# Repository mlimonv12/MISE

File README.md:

View this project on [CADLAB.io](https://cadlab.io/project/28877). 

# MISE

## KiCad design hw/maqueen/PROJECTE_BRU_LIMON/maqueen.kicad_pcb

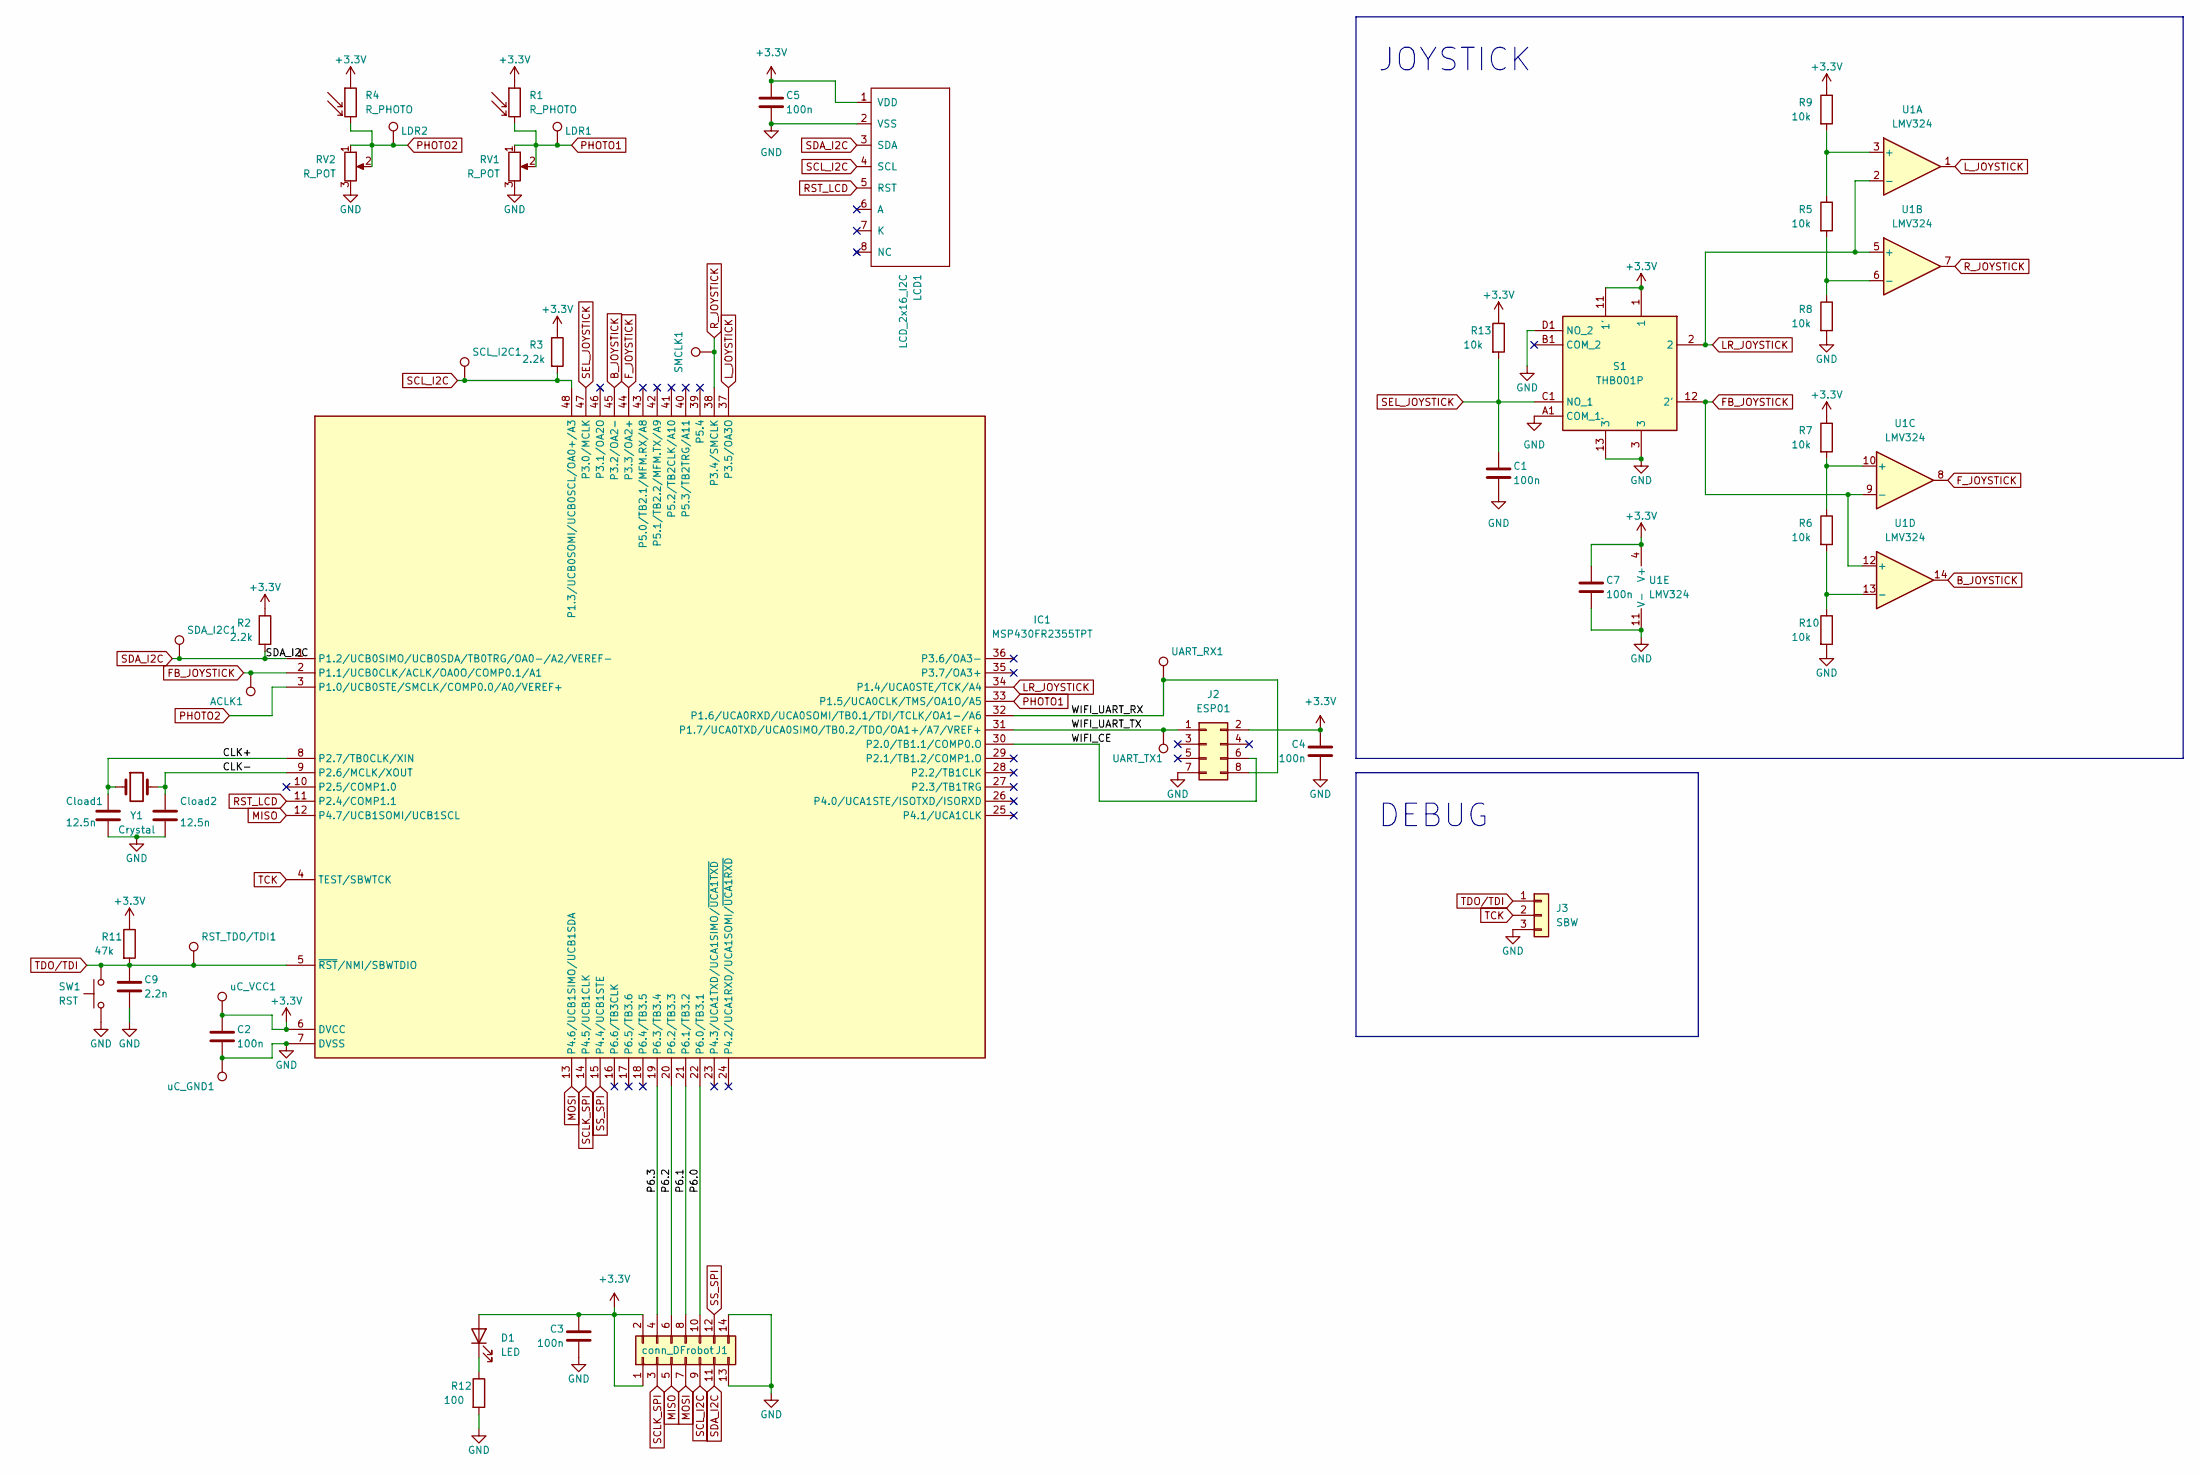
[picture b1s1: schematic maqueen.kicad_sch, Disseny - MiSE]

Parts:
ACLK1: PinHeader_1x01_P2.54mm_Vertical
C1, C2, C3, C4, C5, C7: 100n; C_0805_2012Metric
C9: 2.2n; C_0805_2012Metric
Cload1, Cload2: 12.5n; C_0805_2012Metric
D1: LED; LED_D1.8mm_W3.3mm_H2.4mm
IC1: MSP430FR2355TPT; QFP50P900X900X160-48N; Manufacturer_Part_Number MSP430FR2355TPT; Mouser Part Number 595-MSP430FR2355TPT
J1: conn_DFrobot
J2: ESP01; PinHeader_2x04_P2.54mm_Vertical
J3: SBW; PinHeader_1x03_P2.54mm_Vertical
LCD1: LCD_2x16_I2C; LCD_2x16_I2C(Midas)
LDR1, LDR2: PinHeader_1x01_P2.54mm_Vertical
R1, R4: R_PHOTO; LDR
R2, R3: 2.2k; R_0805_2012Metric
R5, R6, R7, R8, R9, R10, R13: 10k; R_0805_2012Metric
R11: 47k; R_0805_2012Metric
R12: 100; R_0805_2012Metric
RST_TDO/TDI1: PinHeader_1x01_P2.54mm_Vertical
RV1, RV2: R_POT; Trimmer_MiSE
S1: THB001P; Manufacturer_Part_Number THB001P; Mouser Part Number 611-THB001P
SCL_I2C1: PinHeader_1x01_P2.54mm_Vertical
SDA_I2C1: PinHeader_1x01_P2.54mm_Vertical
SMCLK1: PinHeader_1x01_P2.54mm_Vertical
SW1: RST; SW_PUSH_6mm
U1: LMV324; SOIC-14_3.9x8.7mm_P1.27mm
UART_RX1: PinHeader_1x01_P2.54mm_Vertical
UART_TX1: PinHeader_1x01_P2.54mm_Vertical
Y1: Crystal; PinHeader_1x02_P1.27mm_Vertical
uC_GND1: PinHeader_1x01_P2.54mm_Vertical
uC_VCC1: PinHeader_1x01_P2.54mm_Vertical

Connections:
+3.3V: C2.1, C3.1, C4.1, C5.1, C7.1, D1.2 (A), IC1.6 (DVCC), J1.1, J1.2, J2.2, LCD1.1 (VDD), R1.1, R2.1, R3.1, R4.1, R7.1, R9.1, R11.1, R13.1, S1.1, S1.11 (1'), U1.4 (V+), uC_VCC1.1
/CLK+: Cload1.1, IC1.8 (P2.7/TB0CLK/XIN), Y1.1
/CLK-: Cload2.1, IC1.9 (P2.6/MCLK/XOUT), Y1.2
/P6.0: IC1.22 (P6.0/TB3.1), J1.10
/P6.1: IC1.21 (P6.1/TB3.2), J1.8
/P6.2: IC1.20 (P6.2/TB3.3), J1.6
/P6.3: IC1.19 (P6.3/TB3.4), J1.4
/WIFI_CE: IC1.30 (P2.0/TB1.1/COMP0.O), J2.6
/WIFI_UART_RX: IC1.32 (P1.6/UCA0RXD/UCA0SOMI/TB0.1/TDI/TCLK/OA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), J2.8, UART_RX1.1
/WIFI_UART_TX: IC1.31 (P1.7/UCA0TXD/UCA0SIMO/TB0.2/TDO/OA1+/A7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), J2.1, UART_TX1.1
B_JOYSTICK: IC1.45 (P3.2/OA2-), U1.14
FB_JOYSTICK: ACLK1.1, IC1.2 (P1.1/UCB0CLK/ACLK/OA0O/COMP0.1/A1), S1.12 (2'), U1.9 (-), U1.12 (+)
F_JOYSTICK: IC1.44 (P3.3/OA2+), U1.8
GND: C1.2, C2.2, C3.2, C4.2, C5.2, C7.2, C9.2, Cload1.2, Cload2.2, IC1.7 (DVSS), J1.13, J1.14, J2.7, J3.3, LCD1.2 (VSS), R8.2, R10.2, R12.2, RV1.3, RV2.3, S1.3, S1.13 (3'), S1.A1 (COM_1), S1.D1 (NO_2), SW1.1, U1.11 (V-), uC_GND1.1
LR_JOYSTICK: IC1.34 (P1.4/UCA0STE/TCK/A4), S1.2, U1.2 (-), U1.5 (+)
L_JOYSTICK: IC1.37 (P3.5/OA3O), U1.1
MISO: IC1.12 (P4.7/UCB1SOMI/UCB1SCL), J1.5
MOSI: IC1.13 (P4.6/UCB1SIMO/UCB1SDA), J1.7
unnamed: D1.1 (K), R12.1
unnamed: R5.1, R9.2, U1.3 (+)
unnamed: R5.2, R8.1, U1.6 (-)
unnamed: R6.1, R7.2, U1.10 (+)
unnamed: R6.2, R10.1, U1.13 (-)
PHOTO1: IC1.33 (P1.5/UCA0CLK/TMS/OA1O/A5), LDR1.1, R1.2, RV1.1, RV1.2
PHOTO2: IC1.3 (P1.0/UCB0STE/SMCLK/COMP0.0/A0/VEREF+), LDR2.1, R4.2, RV2.1, RV2.2
RST_LCD: IC1.11 (P2.4/COMP1.1), LCD1.5 (RST)
R_JOYSTICK: IC1.38 (P3.4/SMCLK), SMCLK1.1, U1.7
SCLK_SPI: IC1.14 (P4.5/UCB1CLK), J1.3
SCL_I2C: IC1.48 (P1.3/UCB0SOMI/UCB0SCL/OA0+/A3), J1.9, LCD1.4 (SCL), R3.2, SCL_I2C1.1
SDA_I2C: IC1.1 (P1.2/UCB0SIMO/UCB0SDA/TB0TRG/OA0-/A2/VE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), J1.11, LCD1.3 (SDA), R2.2, SDA_I2C1.1
SEL_JOYSTICK: C1.1, IC1.47 (P3.0/MCLK), R13.2, S1.C1 (NO_1)
SS_SPI: IC1.15 (P4.4/UCB1STE), J1.12
TCK: IC1.4 (TEST/SBWTCK), J3.2
TDO/TDI: C9.1, IC1.5 (~RST/NMI/SBWTDIO), J3.1, R11.2, RST_TDO/TDI1.1, SW1.2

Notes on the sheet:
DEBUG
JOYSTICK

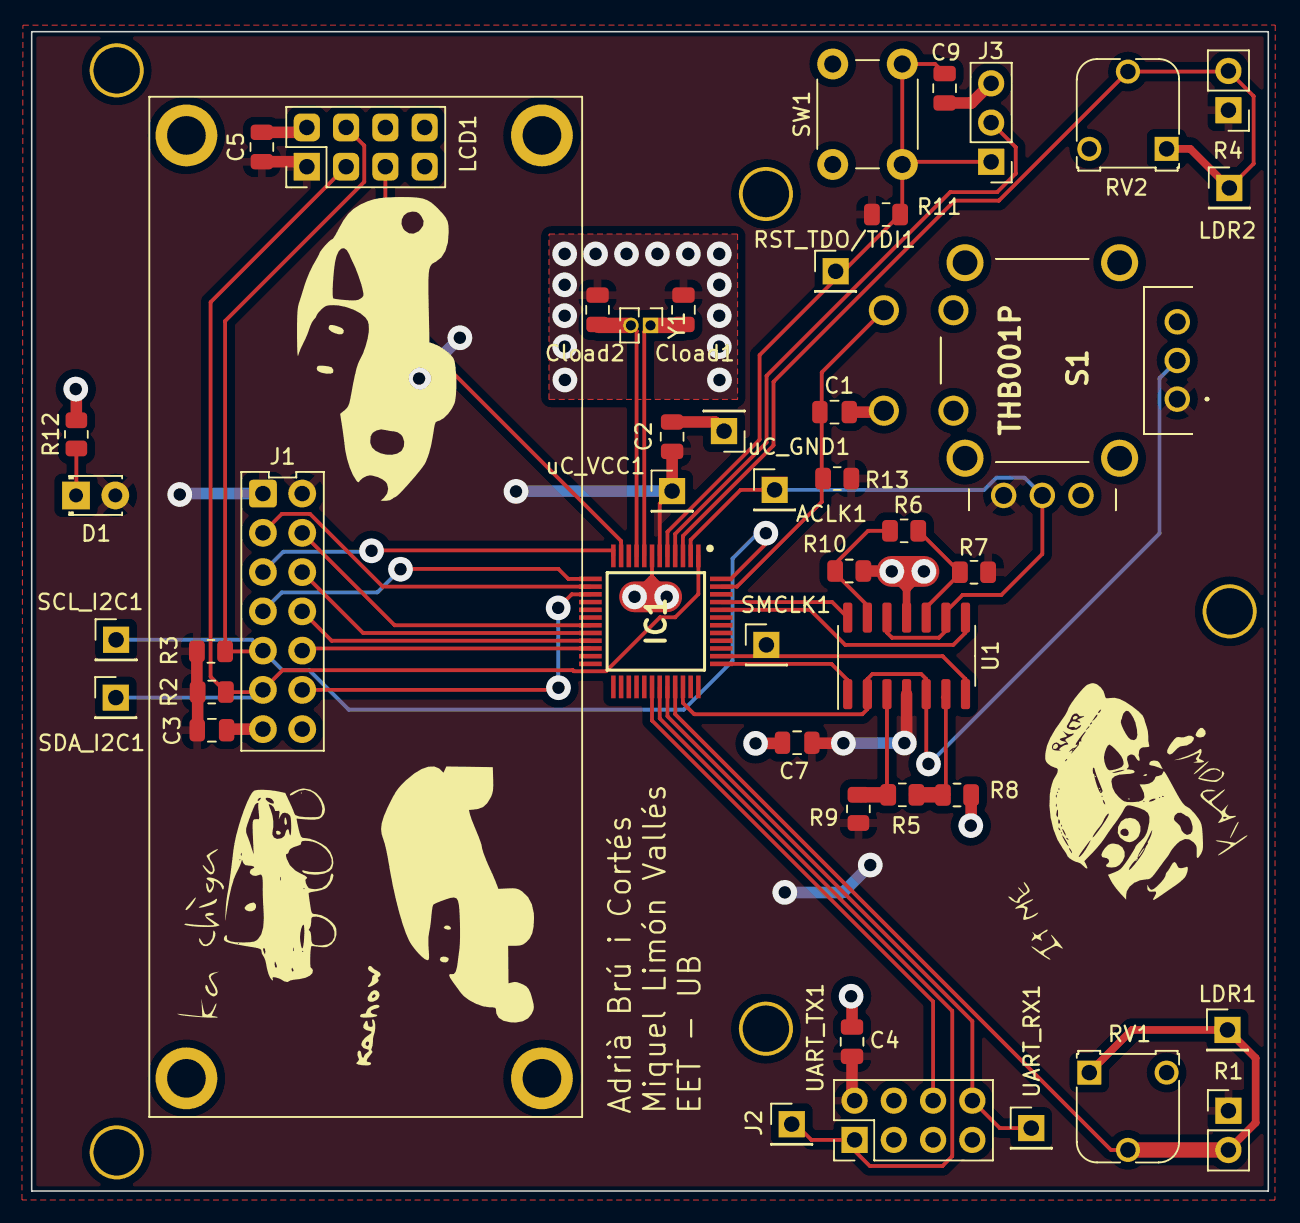
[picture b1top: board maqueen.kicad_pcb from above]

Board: 2 copper layers, 80.0 x 75.0 mm, 45 parts (0 on the bottom side), 34 nets.

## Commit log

2025-02-25 carpeta
2025-02-25 schematic done
2025-02-25 add readme
2025-02-25 constraints + crystal
2025-02-27 netclasses, specs and more
2025-02-27 te toca, miquel
2025-03-01 P6.0-P6.3 intercanviats, joystick i LDRs reordenats. Layout no passa DRC per amplada de THs
2025-03-04 testing points & minor adjustements
2025-03-04 tot drc be, menys huellas i serigrafia
2025-03-04 minor tweaks
2025-03-04 comencem codi
2025-03-07 mogut test points del modul wifi als laterals del connector
2025-03-11 code parts
2025-03-11 afegit pullupR&debounceC a sel_joystick i noms a silkscreen
2025-03-11 i2c builds now
2025-03-17 canvis def disseny
2025-03-18 iron rimenver
2025-03-18 placa corregida
2025-03-18 maqueeeeeeeeeeeeeen
2025-03-18 LEDs + motors funcionen
2025-03-18 follow line
2025-03-18 tests, maybe should revert
2025-03-25 line track works
2025-04-01 nosequinscanvis
2025-04-01 bruh
2025-04-01 i2c lcd començat
2025-04-01 funciona el print amb sprintf
2025-04-08 començat lectura joystick, no funciona interrupcio idk why
2025-04-10 joystick gut
2025-05-03 feina dimarts
2025-05-06 feina 6/5
2025-05-13 ME CAGO EN DIOS
2025-05-13 joystick sembla funcionar
2025-05-20 cosukas
2025-05-20 ADC funciona
2025-05-27 a veh
2025-05-27 ja no se
2025-06-10 cositas wifi
2025-06-11 preliminary lib structure and menu
2025-06-11 builds
2025-06-21 menu movement works and LEDs. LDR callibration doesn't
2025-06-23 some things working
2025-06-24 wifi connection
2025-06-24 wifi menu working
2025-06-24 wifi leds working and motors wip
2025-06-24 motors working
2025-06-24 wifi works perfect
2025-06-24 droidpad working!!!
2025-06-26 joined stuff
2025-06-26 about done
2025-06-26 light follow and escape working fine
2025-06-26 debounce kinda solved
2025-06-26 robot finished
2025-06-26 naming
2025-06-26 intializing wifi
2025-06-26 removed unnecessary comments droidpad
2025-06-26 renaming x)
2025-06-27 comment
2025-06-27 8 samples ADC
2025-06-27 buzzer pipip done
2025-06-27 full buzzer working with wifi
2025-06-27 attempt in wifi.c
2025-06-27 compile
2025-07-01 struct restructure
